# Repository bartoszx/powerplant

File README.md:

# POWERPANEL

_Opis funkcjonalny systemu — retro‑analogowy interfejs do Home Assistanta._

<p align="center">

</p>

_Kliknij, aby powiększyć. Wymiary panelu: 108 × 44 cm._ 

### Spis treści
- [1. Cel i koncepcja projektu](#1-cel-i-koncepcja-projektu)
- [2. Architektura i główne sekcje panelu](#2-architektura-i-główne-sekcje-panelu)
  - [2.1 Płyta główna (Main Board)](#21-płyta-główna-main-board)
  - [2.2 Moduły zewnętrzne](#22-moduły-zewnętrzne)
- [3. Mechanika i interfejs użytkownika](#3-mechanika-i-interfejs-użytkownika)
  - [3.1 Mierniki (sekcja)](#31-mierniki-sekcja)
- [4. Bloki funkcjonalne](#4-bloki-funkcjonalne)
  - [4.1 BLK_METER_ANALOG](#41-blk_meter_analog)
  - [4.2 BLK_METER_LED](#42-blk_meter_led)
  - [4.3 BLK_SWITCHES](#43-blk_switches)
  - [4.4 BLK_CONSOLE](#44-blk_console)
  - [4.5 BLK_SWITCH_LED](#45-blk_switch_led)
- [5. Komunikacja i zasilanie](#5-komunikacja-i-zasilanie)
- [6. Mechanika i ergonomia](#6-mechanika-i-ergonomia)
- [7. Uwagi konstrukcyjne](#7-uwagi-konstrukcyjne)
- [8. Podsumowanie](#8-podsumowanie)
- [9. Pliki schematów i PCB](#9-pliki-schematów-i-pcb)

---

## 1. Cel i koncepcja projektu
PowerPanel to fizyczna interpretacja możliwości systemu Home Assistant — 
czyli materialny, retro-analogowy interfejs do cyfrowego świata automatyki domowej.  

Nie jest to tylko panel energetyczny, ale wielosekcyjny moduł kontrolny i wizualizacyjny,
który odwzorowuje najważniejsze funkcje systemu HA w postaci fizycznych mierników, przycisków, 
przełączników, enkoderów i wskaźników świetlnych.

Celem jest uzyskanie wrażenia „żywego pulpitu sterowniczego” — 
panelu, który reaguje w czasie rzeczywistym na dane z Home Assistanta: energię, temperatury, stany stref, 
tryby pracy, alarmy, a także pozwala na bezpośrednią interakcję z systemem przez dotyk, pokrętła i przełączniki.

Całość utrzymana w stylistyce retro-industrialnej: 
mierniki URAL, bakelitowe przełączniki krzywkowe, suwakowe selektory, 
oraz matowy ekran LCD w stylu terminalowym, wpisujący się w analogowy klimat.

## 2. Architektura i główne sekcje panelu
System składa się z jednej płyty głównej (Main Board) i zestawu płytek peryferyjnych połączonych taśmami IDC.

### 2.1 Płyta główna (Main Board)
Zawiera wszystkie układy logiczne, analogowe i interfejsowe:
- ekspandery MCP23017 (wejścia, przyciski, enkodery),
- przetwornik DAC MCP4728 (sterowanie wskazówkami),
- bufory 74AHCT125 (3.3V → 5V dla WS2812),
- sterowniki ULN2803A (lampki i podświetlenia 12V),
- wzmacniacze LM358 (sterowniki prądowe wskaźników),
- złącza IDC dla modułów zewnętrznych.

<p align="center">
  
</p>

_Wizualizacja 3D płyty głównej (KiCad)._ 

Serce systemu stanowi Raspberry Pi 5, zamontowane bezpośrednio na płycie głównej (formą zbliżone do HAT), zapewniając komunikację, logikę i integrację z Home Assistantem.

Zasilanie:
- 12 V – sekcja mocy i lampek,
- 5 V – LED i DAC,
- 3.3 V – logika i magistrala I²C.
Masę podzielono na GND i GNDPWR (łączone w jednym punkcie).

### 2.2 Moduły zewnętrzne
- **NIXIE BOARD** – sterowanie lampami IN-14 (SPI, wysokonapięciowe).
- **METER PANEL** – z miernikami URAL i podświetleniem LED WS2812.
- **SWITCH PANEL** – sekcja przełączników trybów i zakresów czasowych.
- **CONSOLE PANEL** – centralny moduł z retro-ekranem LCD, enkoderami i kontrolkami.
- **ZONE ADM PANEL** – sekcja administracyjna stref (WAY / GARDEN / ALARM / OPEN).
- **INFO LED BOARD** – lampki 12 V (BIO, REC, OPEN, statusy).

Każdy moduł łączy się z płytą główną przez złącza IDC (10–34 pin).

## 3. Mechanika i interfejs użytkownika
Panel został podzielony na kilka stref funkcjonalnych, rozmieszczonych ergonomicznie na froncie obudowy:

- **Sekcja mierników (górna)** – pięć wskaźników URAL, 
  każdy z osobnym kanałem DAC i LED-podświetleniem.  
  Powyżej nich znajduje się przełącznik krzywkowy pozwalający zmieniać **skalę czasu** (LIVE / 1D / 7D / 14D / 1M / 6M / 12M).

- **Sekcja ZONE ADM (lewa dolna)** – przyciski i lampki strefowe, 
  np. WAY, GARDEN, ALARM, OPEN_PLACE.  
  Każda lampka 12 V jest sterowana z ULN2803A, a przycisk raportuje stan do HA przez I²C.

- **Centralna sekcja sterowania** – retro ekran LCD (terminalowy, tekstowy) 
  pokazujący status systemu i parametry; obok pokrętło **głośności (ENC_VOL)** z ring-LED, 
  przyciski **MODE_A/B/C** (zmiana trybu HA), oraz **przełącznik INPUT/OUTPUT**.

- **Sekcja energetyczna (prawa dolna)** – przełącznik krzywkowy głównego obiegu energetycznego (np. GRID / BAT / ISLAND),
  kontrolki statusu ładowania, oraz wskaźnik prądu zasilania głównego.

- **Selektor temperatury (prawy górny)** – przełącznik suwakowy wybierający, 
  które pomieszczenie ma być aktualnie wskazywane na mierniku temperatury (OUTDOOR / SALON / GAB / MIB / HEL / OLA).

Każdy element panelu ma fizyczne sprzężenie zwrotne: ruch wskazówki, światło LED, dźwięk enkodera, klik przełącznika.  
To czyni PowerPanel prawdziwie materialnym interfejsem Home Assistanta.

### 3.1 Mierniki (sekcja)
<p align="center">

</p>

_Tarcza, render sekcji i płytka z 30 micro‑LED — kliknij, aby powiększyć._

Na schemacie wyjścia prowadzące do poszczególnych mierników oznaczone są ich pierwotnymi parametrami (np. „2A”, „25mA”). Oznaczenia te służą pamięci i kalibracji podczas strojenia układu.

Każdy miernik, poza podstawowym działaniem pomiarowym, został zmodyfikowany:
- pod główną skalą umieszczono 30 programowalnych micro‑LEDów, pozwalających tworzyć efekty świetlne i subtelne wskazania kontekstowe,
- dodatkowy LED podświetla tarczę, poprawiając czytelność w słabym oświetleniu.

## 4. Bloki funkcjonalne

### 4.1 BLK_METER_ANALOG
Sterowanie pięcioma miernikami URAL.  
Układy: MCP4728 + LM358 + tranzystory 2N2222A.  
Każdy kanał DAC generuje napięcie (0–5 V) → LM358 → tranzystor NPN → cewka miernika.  
Filtry RC (100 nF + 10 kΩ) wygładzają wskazanie.  
Zasilanie 5 V, masa GNDPWR.  
Kanały: SENSE_A–E (MTR1–MTR5).

---

### 4.2 BLK_METER_LED
Sterowanie LED WS2812 i przyciskami 12 V w sekcji mierników i przycisków.  
Układy: MCP23017, ULN2803A ×2, 74AHCT125 ×2.  
Port A MCP23017 steruje ULN2803A (OUT_Mx_BL, URAL).  
Port B obsługuje przyciski i kontrolki (BTN_GATE, GARAGE, DOOR itd.).  
Bufory 74AHCT125 translatują sygnały LED 3.3V → 5V (MTR1–MTR5).  
Rezystory 68 Ω w szereg z liniami danych.  
Lampki 12 V sterowane z ULN2803A (open collector).  
GND i GNDPWR łączone w jednym punkcie.

---

### 4.3 BLK_SWITCHES
Sekcja 12 przełączników (tryby + zakresy) i 4 przyciski ZONE ADM.  
Układ: MCP23017 @ 0x21.  
Wejścia z pull-up 10 kΩ, C=100 nF do GND (debounce).  
Złącza:  
- IDC-20_SWITCH_BUS – tryby pracy (AUTO, BAT-SAVE, BLACKOUT, itp.)  
- IDC-12_SWITCH_ZONE_BUS – strefy (WAY, GARDEN, ALARM, OPEN)  
Stany czytane przez I²C.

---

### 4.4 BLK_CONSOLE
Centralny panel z trzema enkoderami i przyciskami MODE.  
Układ: MCP23017 @ 0x23.  
Pull-up 10 kΩ + C=100 nF (debounce).  
Linia INT_CONSOLED (opcjonalne przerwanie).  
Złącze IDC-16_CONSOLE:  
- MODE_A/B/C – wybór trybów  
- ENC_VOL, ENC_TOP, ENC_BOTTOM – enkodery  
- VOL_RING_DATA – dane LED pierścienia  
- przyciski push – w osi enkoderów

---

### 4.5 BLK_SWITCH_LED
Buforowanie danych LED (74AHCT125) i sterowanie lampkami 12 V (ULN2803A).  
Złącza:  
- IDC-10_SWITCH_LED_DATA – LED WS2812  
- IDC-6_ZONE_INFO_12V – lampki BIO / REC / OPEN  
Sygnały 3.3V z RPi → bufory 5V → taśmy WS2812.  
Rezystory R58–R60 = 100 Ω.  
Wspólna masa GND↔GNDPWR.

---

## 5. Komunikacja i zasilanie
Magistrala I²C:
- MCP23017 (SWITCHES) – 0x21  
- MCP23017 (CONSOLE) – 0x23  
- MCP23017 (METER_LED) – 0x20  
- MCP4728 (METER_ANALOG) – 0x60  

Zasilanie:
- +12 V – lampki i przekaźniki  
- +5 V – LED WS2812, DAC  
- +3.3 V – logika i I²C  
- GND / GNDPWR – wspólny punkt (separacja prądów)

---

## 6. Mechanika i ergonomia
- Wskaźniki URAL – analogowe sprzężenie ruchu z DAC.  
- LED – efekt tła i animacje w rytmie danych HA.  
- Przyciski 12 V – kontrola stref / trybów.  
- Enkodery – głośność, tryby, ustawienia.  
- Krzywkowe i suwakowe selektory – wybór skali czasu, temperatury, źródła energii.  
- Retro LCD – dane systemowe i statusy HA.  

- Panel frontowy z blachy stalowej zostanie poddany kontrolowanemu procesowi postarzenia (patyna, przetarcia, delikatnie pordzewiałe krawędzie), aby uzyskać wygląd starego, przemysłowego urządzenia.

Każdy element ma bezpośrednią funkcję w HA i wizualne potwierdzenie akcji.

---

## 7. Uwagi konstrukcyjne
- Separacja GND / GNDPWR.  
- Stitching vias między planami mas.  
- 100 nF przy każdym układzie.  
- Rezystory szeregowe 68–100 Ω przy WS2812.  
- C = 1000 µF przy zasilaniu LED.  
- LM358 i MCP4728 zasilane z 5 V (z odniesieniem do GNDPWR).  
- Bufory 74AHCT125 – VCC = 5 V, Vih ≥ 2 V.

---

## 8. Podsumowanie
PowerPanel to fizyczny interfejs Home Assistanta — 
łączący dane z automatyki, energii, stref, mediów i systemów bezpieczeństwa w jednym, dotykalnym pulpicie.

Zawiera:
- 5 analogowych mierników URAL (DAC-sterowane),
- 3 enkodery + ring LED,
- 20+ LED WS2812,
- 20 przycisków i przełączników,
- kontrolki 12 V,
- wyświetlacz LCD retro,
- oraz krzywkowe i suwakowe selektory trybów.

Stanowi pomost między cyfrowym systemem automatyki a fizycznym światem.

---

## 9. Pliki schematów i PCB

**Źródło prawdy (source of truth)** dla hardware'u: **`hardware/pcb/powerplant.kicad_sch`**.  
Ten plik może się aktualizować; dokumentacja, konfiguracja i kod powinny być z nim zsynchronizowane.

Pliki KiCad znajdują się w katalogu `hardware/pcb`:

- Główne pliki projektu: `hardware/pcb/powerplant.kicad_sch`, `hardware/pcb/powerplant.kicad_pcb`
- Schematy bloków: 
  - `hardware/pcb/BLK_BUTTONS.kicad_sch`
  - `hardware/pcb/BLK_CONSOLE.kicad_sch`
  - `hardware/pcb/BLK_METER_LED.kicad_sch`
  - `hardware/pcb/BLK_SWITCH_LED.kicad_sch`
  - `hardware/pcb/BLK_SWITCHES.kicad_sch`

Pełne drzewo plików sprzętowych: `hardware/pcb/`.

**Moduł sterowania miernikami** (osobny projekt KiCad, pliki w Dropbox: `kicad/powerplant/modul-miernikow.*`):

- Opis schematu (weryfikacja MCP): [`doc/modul-miernikow-opis-schematu.md`](doc/modul-miernikow-opis-schematu.md)
- Wklejka na schemat KiCad: [`doc/modul-miernikow-wklejka-schemat.txt`](doc/modul-miernikow-wklejka-schemat.txt)

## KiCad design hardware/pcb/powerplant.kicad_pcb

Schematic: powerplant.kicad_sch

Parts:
A1: RaspberryPi_Pico; RaspberryPi_Pico_Common_Unspecified
C1, C8, C11, C13, C18, C20: 4.7 µF; R_1206_3216Metric
C2, C3, C6, C7, C10, C12, C16, C17, C19, C59, C60, C61: 100 nF; C_0603_1608Metric
C4, C29: 10 µF; R_1206_3216Metric
C5, C9, C14, C15, C21, C22: 680 pF; C_0603_1608Metric
C53, C58: 1 µF; C_0603_1608Metric
C54: 4.7 µF; C_0603_1608Metric
FB2: FerriteBead 600 Ω @ 100 MHz; L_1206_3216Metric_Pad1.22x1.90mm_HandSolder
J2: J_AUX; JST_PH_B8B-PH-K_1x08_P2.00mm_Vertical
J3: VL53L0X; JST_PH_B4B-PH-K_1x04_P2.00mm_Vertical
J4: J_LCD_PWR; JST_PH_B2B-PH-K_1x02_P2.00mm_Vertical
J5: SPARE; JST_PH_B8B-PH-K_1x08_P2.00mm_Vertical
J6: RPi_GPIO; RPI_Hat_B_NOPCB
J16: 14_NIXIE_BUS; IDC-Header_2x07_P2.54mm_Vertical
J19: J_LIGHT; JST_PH_B4B-PH-K_1x04_P2.00mm_Vertical
J21: IDC-10_METER_SIG; IDC-Header_2x05_P2.54mm_Vertical
J22: J_IN; SolderWire-1sqmm_1x02_P5.4mm_D1.4mm_OD2.7mm
J23: J_OUT; SolderWire-1sqmm_1x02_P5.4mm_D1.4mm_OD2.7mm
J24: POWER IN 12V; BarrelJack_Horizontal
NT1: NetTie_2; NetTie-2_THT_Pad1.0mm
Q1, Q2, Q3, Q4, Q5, Q6: IRLZ44N; TO-220-3_Vertical
R1, R5, R9, R10, R21, R22: 10 kΩ; R_0603_1608Metric
R2, R6, R11, R12, R23, R24: 100 Ω; R_1206_3216Metric_Pad1.30x1.75mm_HandSolder
R3, R15: Rlimit 100 kΩ; R_0603_1608Metric
R4, R8, R13, R14, R25, R26: Rpd 100 kΩ; R_0603_1608Metric
R7: Rlimit 150 kΩ; R_0603_1608Metric
R16, R29, R30: Rlimit 10 Ω; R_0603_1608Metric
R17, R20: RSENSE 200 kΩ; R_0603_1608Metric
R18: RSENSE 140 kΩ; R_0603_1608Metric
R19: RSENSE 500 Ω; R_0603_1608Metric
R27, R28: RSENSE 820 Ω; R_0603_1608Metric
R62, R63: 4.7kΩ; R_0603_1608Metric
U1, U4: MCP4728; MSOP-10_3x3mm_P0.5mm
U2, U3, U10: LM358_DFN; DFN-8-1EP_2x2mm_P0.5mm_EP1.05x1.75mm
U14: TPS22917DBV; SOT-23-6

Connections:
+3.3V: FB2.1, J5.1, J6.1 (3.3V), R62.1, R63.1; also elsewhere on the board
+5V: A1.40 (VBUS), C6.2, C16.2, C53.2, J3.4, J6.2 (5V), J16.1, J16.10, J23.1, U1.1 (VDD), U4.1 (VDD), U14.1 (VIN); also elsewhere on the board
+12V: C3.1, C4.1, C29.1, C60.1, C61.1, J22.1, J24.1, R3.1, R7.1, R15.1, R16.1, R29.2, R30.2, U2.8 (V+), U3.8 (V+), U10.8 (V+); also elsewhere on the board
/AUX_I2S_LRCLK: J2.2, J6.35 (BCM19_MISO_PCM_FS)
/AUX_I2S_RX: J2.4, J6.38 (BCM20_MOSI_PCM_DI)
/AUX_I2S_TX: J2.3, J6.40 (BCM21_SCLK_PCM_DO)
/AUX_SCL: J2.6, J3.2, J6.5 (BCM3_SCL), J19.4, R62.2, U1.2 (SCL), U4.2 (SCL); also elsewhere on the board
/AUX_SDA: J2.5, J3.3, J6.3 (BCM2_SDA), J19.3, R63.2, U1.3 (SDA), U4.3 (SDA); also elsewhere on the board
/BLK_CONSOLE/INT_CONSOLE: J6.21 (BCM9_MISO); also elsewhere on the board
/BLK_METER_LED/CTRL_GARAGE_LED: J6.16 (BCM23); also elsewhere on the board
/BLK_METER_LED/CTRL_GATE_LED: J6.18 (BCM24); also elsewhere on the board
/BLK_METER_LED/GPIO_LED1: A1.9 (GPIO6); also elsewhere on the board
/BLK_METER_LED/GPIO_LED2: A1.10 (GPIO7); also elsewhere on the board
/BLK_METER_LED/GPIO_LED3: A1.11 (GPIO8); also elsewhere on the board
/BLK_METER_LED/GPIO_LED4: A1.12 (GPIO9); also elsewhere on the board
/BLK_METER_LED/GPIO_LED5: A1.14 (GPIO10); also elsewhere on the board
/BLK_METER_LED/GPIO_VOL_RING: A1.7 (GPIO5); also elsewhere on the board
/BLK_SWITCH_LED/LED_MODE_DATA_IN: A1.5 (GPIO3); also elsewhere on the board
/BLK_SWITCH_LED/LED_RANGE_DATA_IN: A1.4 (GPIO2); also elsewhere on the board
/BLK_SWITCH_LED/LED_TEMP_DATA_IN: A1.6 (GPIO4); also elsewhere on the board
/CTRL_INFO_BIO: J6.15 (BCM22); also elsewhere on the board
/CTRL_INFO_OPEN: J6.11 (BCM17); also elsewhere on the board
/CTRL_INFO_REC: J6.13 (BCM27); also elsewhere on the board
/GP0_TX_PICO: A1.1 (GPIO0), J6.10 (BCM15_RXD)
/GP1_RX_PICO: A1.2 (GPIO1), J6.8 (BCM14_TXD)
/GP11: A1.15 (GPIO11), J5.3
/GP12: A1.16 (GPIO12), J5.4
/GP13: A1.17 (GPIO13), J5.5
/GP14: A1.19 (GPIO14), J5.6
/GP15: A1.20 (GPIO15), J5.7
/GP16: A1.21 (GPIO16), J5.8
/J_METER_1A+: J21.5, R15.2
/J_METER_5mA+: J21.3, R7.2
/J_METER_25uA+: J21.1, R3.2
/J_METER_PLUS_MINUS+: J21.9, Q5.2 (D), R29.1
/J_METER_TBC+: J21.7, R16.2
/LCD_PWR_EN: J6.12 (BCM18_PCM_C), U14.3 (ON)
/METER-: J21.2, Q1.2 (D)
/MR: J21.10, Q6.2 (D), R30.1
/NIXIE_CS1: J6.24 (BCM8_CE0), J16.5
/NIXIE_CS2: J6.26 (BCM7_CE1), J16.6
/NIXIE_CS3: J6.22 (BCM25), J16.7
/NIXIE_CS4: J6.27 (BCM0_ID_SD), J16.8
/SENSE_A: C5.2, Q1.3 (S), R17.2, U2.2 (-)
/SENSE_B: C9.2, Q2.3 (S), R18.2, U2.6 (-)
/SENSE_C: C14.2, Q3.3 (S), R19.2, U3.2 (-)
/SENSE_D: C15.2, Q4.3 (S), R20.2, U3.6 (-)
/SENSE_E1: C21.2, Q5.3 (S), R27.1, U10.2 (-)
/SENSE_E2: C22.2, Q6.3 (S), R28.1, U10.6 (-)
/SPI_MOSI: J6.19 (BCM10_MOSI), J16.3
/SPI_SCLK: J6.23 (BCM11_SCLK), J16.4
/VIN_FILT_A: R1.1, U1.6 (VOUTA), U2.3 (+)
/VIN_FILT_B: R5.1, U1.7 (VOUTB), U2.5 (+)
/VIN_FILT_C: R9.1, U1.8 (VOUTC), U3.3 (+)
/VIN_FILT_D: R10.1, U1.9 (VOUTD), U3.5 (+)
/VIN_FILT_E1: R21.1, U4.6 (VOUTA), U10.3 (+)
/VIN_FILT_E2: R22.1, U4.7 (VOUTB), U10.5 (+)
GND: A1.3 (GND), A1.8 (GND), A1.13 (GND), A1.18 (GND), A1.23 (GND), A1.28 (GND), A1.38 (GND), C6.1, C16.1, C53.1, C54.2, C58.1, C59.1, J2.7, J3.1, J4.2, J5.2, J6.39 (GND), J16.2, J16.11, J16.12, J19.2, J23.2, NT1.1, U1.10 (VSS), U4.10 (VSS), U14.2 (GND); also elsewhere on the board
GNDPWR: C1.2, C2.1, C3.2, C4.2, C7.1, C8.2, C10.1, C11.2, C12.1, C13.2, C17.1, C18.2, C19.1, C20.2, C29.2, C60.2, C61.2, J22.2, J24.2, NT1.2, R4.2, R8.2, R13.2, R14.2, R17.1, R18.1, R19.1, R20.1, R25.1, R26.1, R27.2, R28.2, U2.4 (V-), U2.9 (PAD), U3.4 (V-), U3.9 (PAD), U10.4 (V-), U10.9 (PAD); also elsewhere on the board
unnamed: C1.1, C2.2, R1.2
unnamed: C5.1, R2.1, U2.1
unnamed: C7.2, C8.1, R5.2
unnamed: C9.1, R6.1, U2.7
unnamed: C10.2, C11.1, R9.2
unnamed: C12.2, C13.1, R10.2
unnamed: C14.1, R11.1, U3.1
unnamed: C15.1, R12.1, U3.7
unnamed: C17.2, C18.1, R21.2
unnamed: C19.2, C20.1, R22.2
unnamed: C21.1, R23.1, U10.1
unnamed: C22.1, R24.1, U10.7
unnamed: C54.1, J4.1, U14.6 (VOUT)
unnamed: C58.2, C59.2, FB2.2, J19.1
unnamed: J21.4, Q2.2 (D)
unnamed: J21.6, Q3.2 (D)
unnamed: J21.8, Q4.2 (D)
unnamed: Q1.1 (G), R2.2, R4.1
unnamed: Q2.1 (G), R6.2, R8.1
unnamed: Q3.1 (G), R11.2, R13.1
unnamed: Q4.1 (G), R12.2, R14.1
unnamed: Q5.1 (G), R23.2, R25.2
unnamed: Q6.1 (G), R24.2, R26.2

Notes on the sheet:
⚙️ BLK_METER_ANALOG - opis funkcjonalny ======================================== Sekcja: Tory sterowania i pomiaru wskaźników analogowych (5 kanałów VU / mA / wskazówki URAL) Układy główne: U3A-U3E, U10A-U10C - LM358 (wzmacniacze operacyjne) U1 - MCP4728 (4-kanałowy DAC I²C, 12-bit) Q1-Q5 - tranzys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
CZUJNIK SWIATLA
NIXIE zew board https://github.com/dekuNukem/exixe po SPI

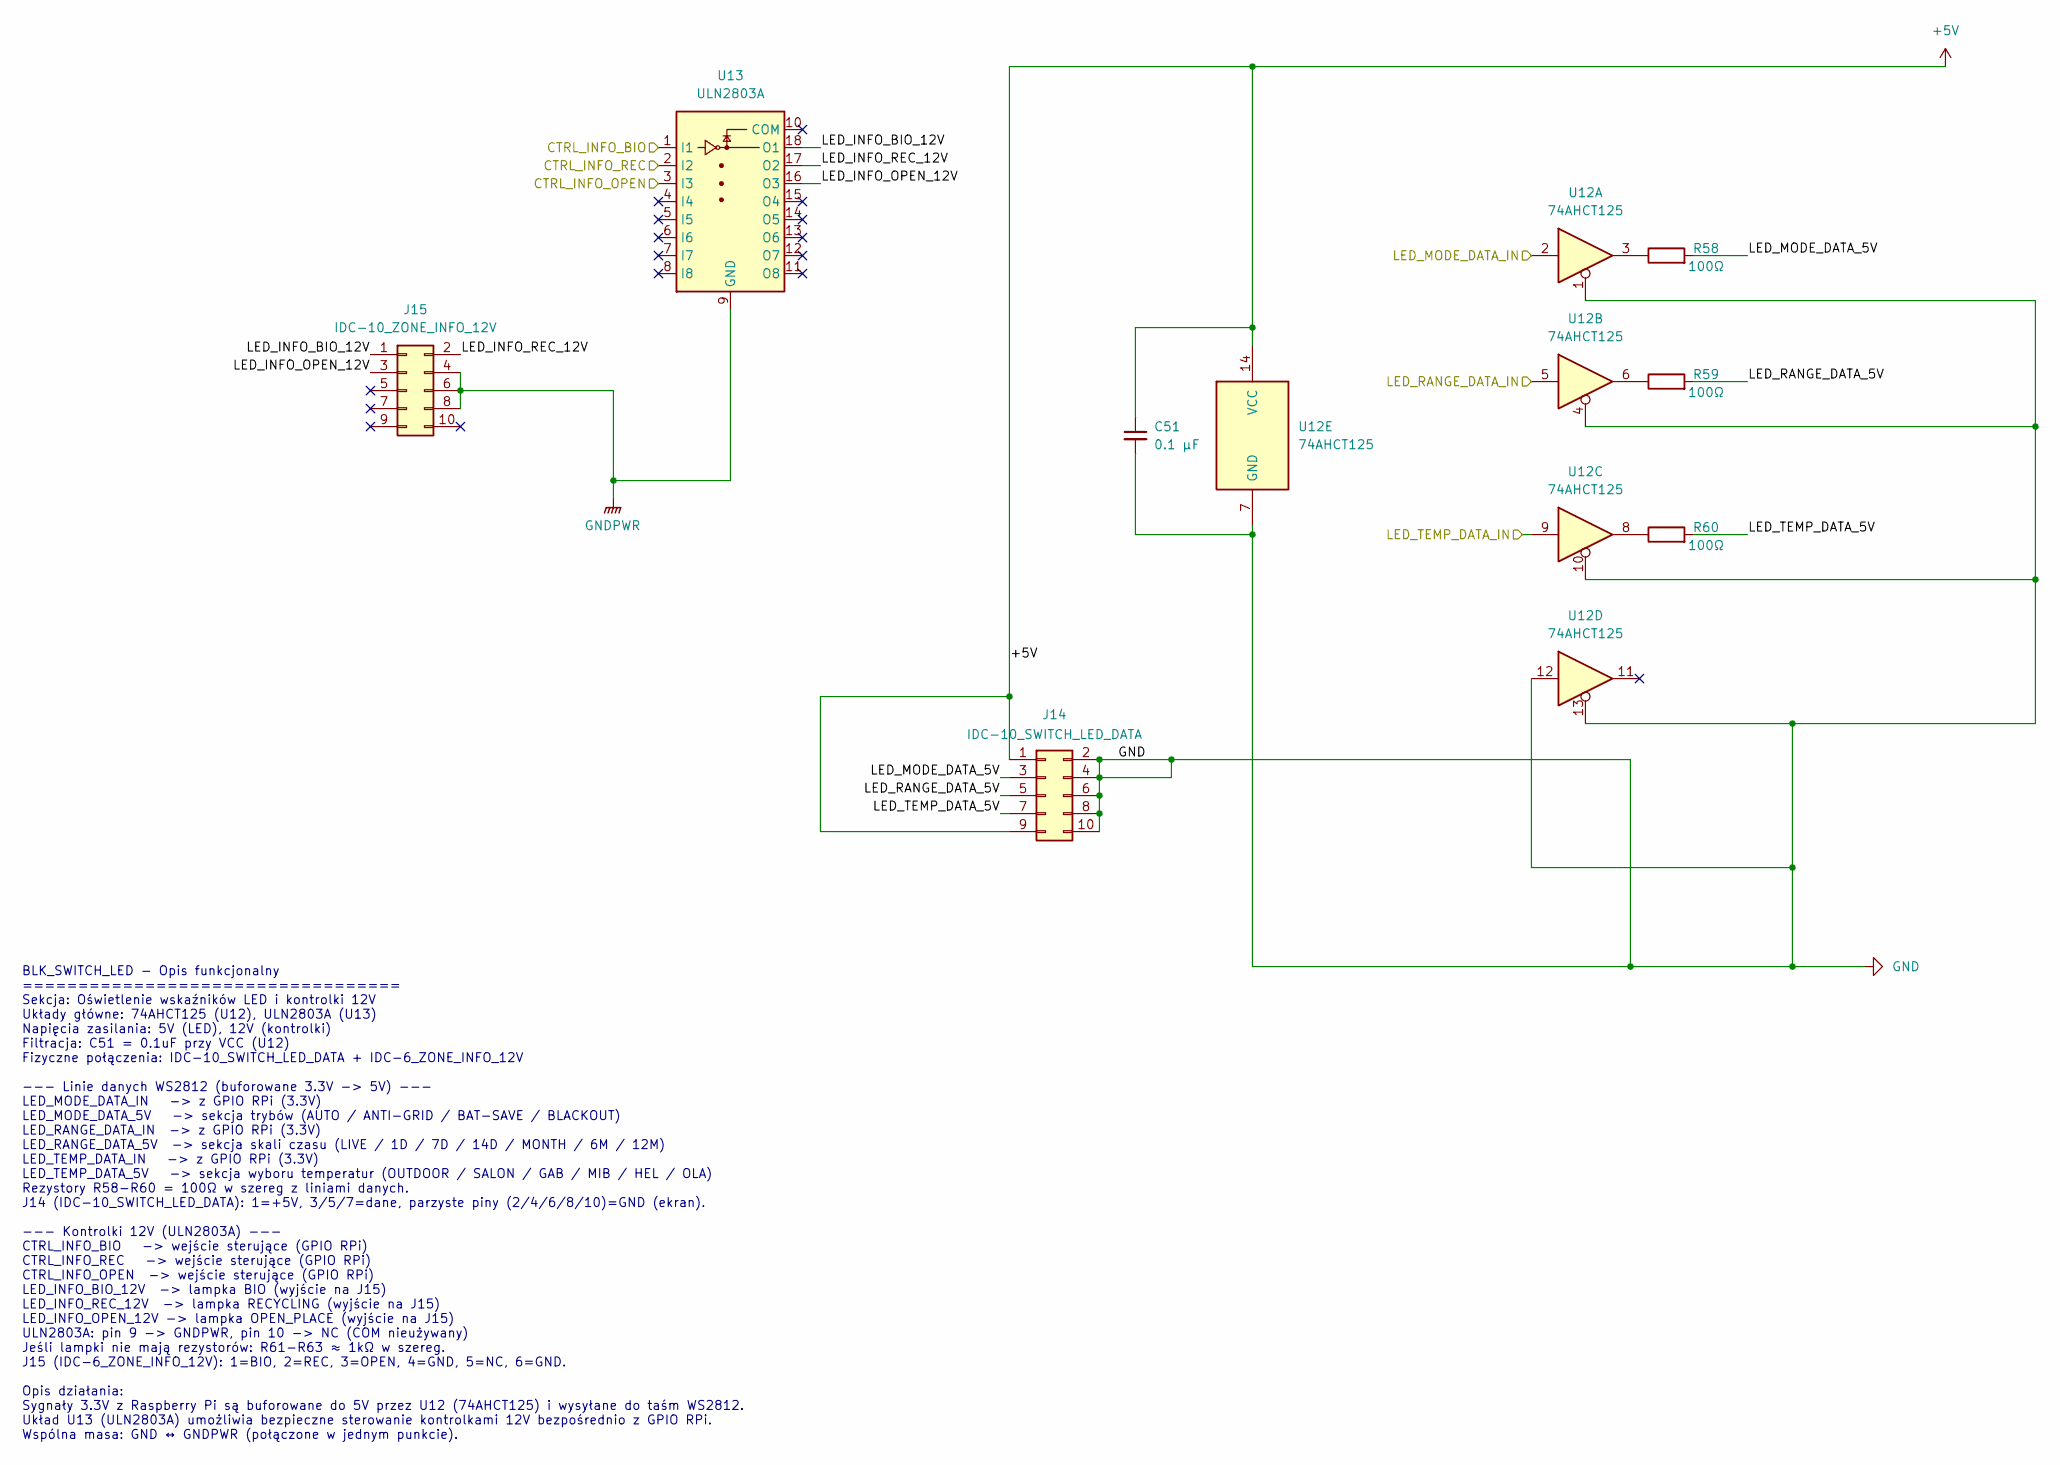
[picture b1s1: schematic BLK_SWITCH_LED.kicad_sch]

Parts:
C51: 0.1 µF; C_0603_1608Metric
J14: IDC-10_SWITCH_LED_DATA; IDC-Header_2x05_P2.54mm_Vertical
J15: IDC-10_ZONE_INFO_12V; IDC-Header_2x05_P2.54mm_Vertical
R58, R59, R60: 100Ω; R_0603_1608Metric
U12: 74AHCT125; SOIC-14_3.9x8.7mm_P1.27mm
U13: ULN2803A; SSOP-18_4.4x6.5mm_P0.65mm

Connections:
+5V: C51.1, J14.1, J14.9, U12.14 (VCC); also elsewhere on the board
/BLK_SWITCH_LED/LED_INFO_BIO_12V: J15.1, U13.18 (O1)
/BLK_SWITCH_LED/LED_INFO_OPEN_12V: J15.3, U13.16 (O3)
/BLK_SWITCH_LED/LED_INFO_REC_12V: J15.2, U13.17 (O2)
/BLK_SWITCH_LED/LED_MODE_DATA_5V: J14.3, R58.2
/BLK_SWITCH_LED/LED_MODE_DATA_IN: U12.2; also elsewhere on the board
/BLK_SWITCH_LED/LED_RANGE_DATA_5V: J14.5, R59.2
/BLK_SWITCH_LED/LED_RANGE_DATA_IN: U12.5; also elsewhere on the board
/BLK_SWITCH_LED/LED_TEMP_DATA_5V: J14.7, R60.2
/BLK_SWITCH_LED/LED_TEMP_DATA_IN: U12.9; also elsewhere on the board
/CTRL_INFO_BIO: U13.1 (I1); also elsewhere on the board
/CTRL_INFO_OPEN: U13.3 (I3); also elsewhere on the board
/CTRL_INFO_REC: U13.2 (I2); also elsewhere on the board
GND: C51.2, J14.2, J14.4, J14.6, J14.8, J14.10, U12.1, U12.4, U12.7 (GND), U12.10, U12.12, U12.13; also elsewhere on the board
GNDPWR: J15.4, J15.6, J15.8, U13.9 (GND); also elsewhere on the board
unnamed: R58.1, U12.3
unnamed: R59.1, U12.6
unnamed: R60.1, U12.8

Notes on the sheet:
BLK_SWITCH_LED - Opis funkcjonalny ================================== Sekcja: Oświetlenie wskaźników LED i kontrolki 12V Układy główne: 74AHCT125 (U12), ULN2803A (U13) Napięcia zasilania: 5V (LED), 12V (kontrolki) Filtracja: C51 = 0.1uF przy VCC (U12) Fizyczne połączenia: IDC-10_SWITCH_LED_DATA + I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

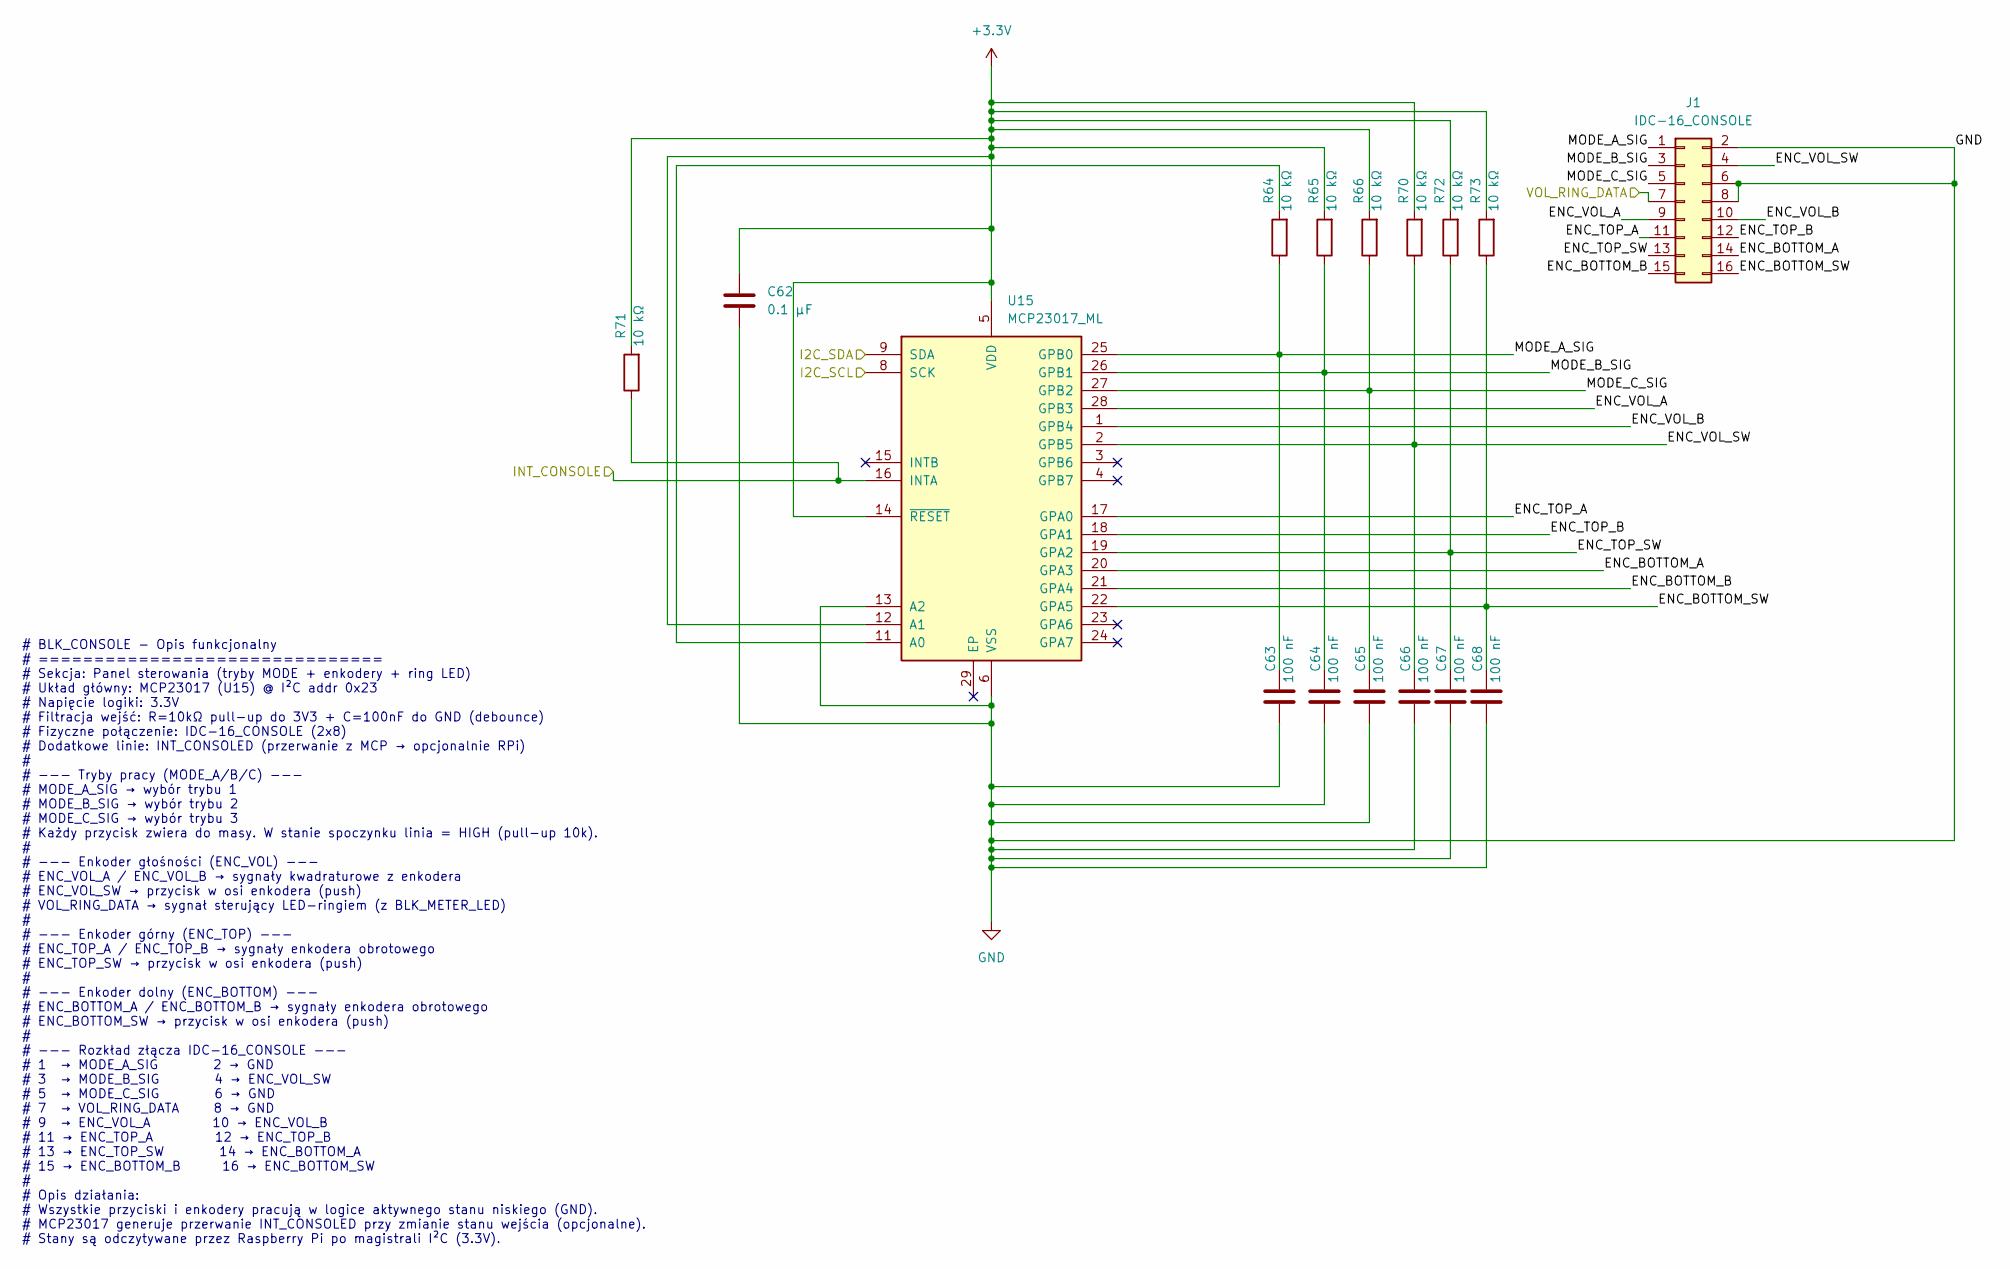
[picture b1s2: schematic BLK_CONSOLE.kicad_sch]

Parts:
C62: 0.1 µF; C_1206_3216Metric_Pad1.33x1.80mm_HandSolder
C63, C64, C65, C66, C67, C68: 100 nF; C_1206_3216Metric_Pad1.33x1.80mm_HandSolder
J1: IDC-16_CONSOLE; IDC-Header_2x08_P2.54mm_Vertical
R64, R65, R66, R70, R71, R72, R73: 10 kΩ; R_1206_3216Metric_Pad1.30x1.75mm_HandSolder
U15: MCP23017_ML; QFN-28-1EP_6x6mm_P0.65mm_EP4.25x4.25mm

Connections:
+3.3V: C62.2, R65.2, R66.2, R70.2, R71.2, R72.2, R73.2, U15.5 (VDD), U15.12 (A1), U15.14 (~RESET); also elsewhere on the board
/AUX_SCL: U15.8 (SCK); also elsewhere on the board
/AUX_SDA: U15.9 (SDA); also elsewhere on the board
/BLK_CONSOLE/ENC_BOTTOM_A: J1.14, U15.20 (GPA3)
/BLK_CONSOLE/ENC_BOTTOM_B: J1.15, U15.21 (GPA4)
/BLK_CONSOLE/ENC_BOTTOM_SW: C68.2, J1.16, R73.1, U15.22 (GPA5)
/BLK_CONSOLE/ENC_TOP_A: J1.11, U15.17 (GPA0)
/BLK_CONSOLE/ENC_TOP_B: J1.12, U15.18 (GPA1)
/BLK_CONSOLE/ENC_TOP_SW: C67.2, J1.13, R72.1, U15.19 (GPA2)
/BLK_CONSOLE/ENC_VOL_A: J1.9, U15.28 (GPB3)
/BLK_CONSOLE/ENC_VOL_B: J1.10, U15.1 (GPB4)
/BLK_CONSOLE/ENC_VOL_SW: C66.2, J1.4, R70.1, U15.2 (GPB5)
/BLK_CONSOLE/INT_CONSOLE: R71.1, U15.16 (INTA); also elsewhere on the board
/BLK_CONSOLE/MODE_A_SIG: C63.2, J1.1, R64.1, U15.25 (GPB0)
/BLK_CONSOLE/MODE_B_SIG: C64.2, J1.3, R65.1, U15.26 (GPB1)
/BLK_CONSOLE/MODE_C_SIG: C65.2, J1.5, R66.1, U15.27 (GPB2)
/BLK_CONSOLE/VOL_RING_DATA: J1.7; also elsewhere on the board
GND: C62.1, C63.1, C64.1, C65.1, C66.1, C67.1, C68.1, J1.2, J1.6, J1.8, U15.6 (VSS), U15.13 (A2); also elsewhere on the board
unnamed: R64.2, U15.11 (A0)

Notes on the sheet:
# BLK_CONSOLE - Opis funkcjonalny # =============================== # Sekcja: Panel sterowania (tryby MODE + enkodery + ring LED) # Układ główny: MCP23017 (U15) @ I²C addr 0x23 # Napięcie logiki: 3.3V # Filtracja wejść: R=10kΩ pull-up do 3V3 + C=100nF do GND (debounce) # Fizyczne połączenie: IDC-16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

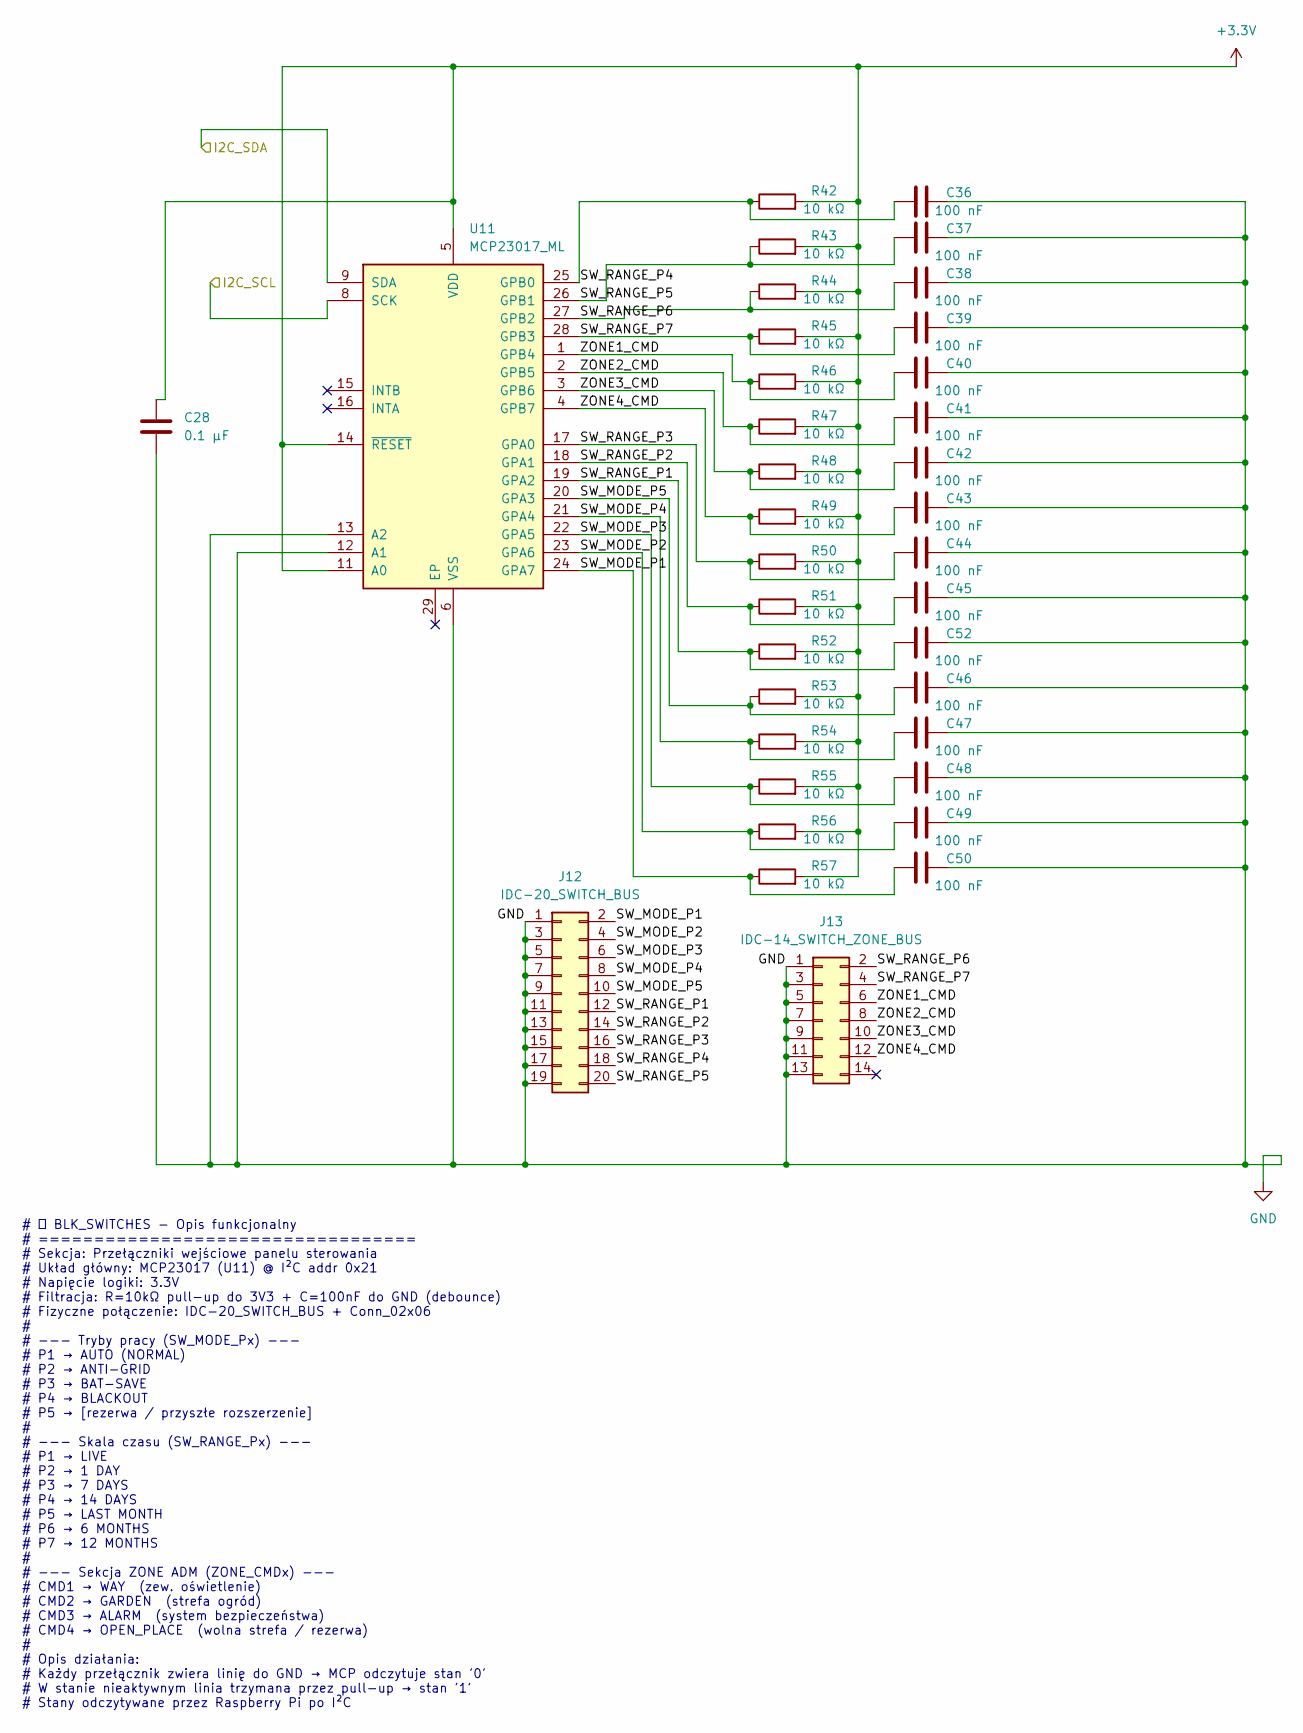
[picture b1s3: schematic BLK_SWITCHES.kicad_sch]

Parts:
C28: 0.1 µF; C_1206_3216Metric_Pad1.33x1.80mm_HandSolder
C36, C37, C38, C39, C40, C41, C42, C43, C44, C45, C46, C47, C48, C49, C50, C52: 100 nF; C_1206_3216Metric_Pad1.33x1.80mm_HandSolder
J12: IDC-20_SWITCH_BUS; IDC-Header_2x10_P2.54mm_Vertical
J13: IDC-14_SWITCH_ZONE_BUS; IDC-Header_2x07_P2.54mm_Vertical
R42, R43, R44, R45, R46, R47, R48, R49, R50, R51, R52, R53, R54, R55, R56, R57: 10 kΩ; R_1206_3216Metric_Pad1.30x1.75mm_HandSolder
U11: MCP23017_ML; QFN-28-1EP_6x6mm_P0.65mm_EP4.25x4.25mm

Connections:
+3.3V: C28.2, R42.2, R43.2, R44.2, R45.2, R46.2, R47.2, R48.2, R49.2, R50.2, R51.2, R52.2, R53.2, R54.2, R55.2, R56.2, R57.2, U11.5 (VDD), U11.11 (A0), U11.14 (~RESET); also elsewhere on the board
/AUX_SCL: U11.8 (SCK); also elsewhere on the board
/AUX_SDA: U11.9 (SDA); also elsewhere on the board
/BLK_SWITCHES/SW_MODE_P1: C50.1, J12.2, R57.1, U11.24 (GPA7)
/BLK_SWITCHES/SW_MODE_P2: C49.1, J12.4, R56.1, U11.23 (GPA6)
/BLK_SWITCHES/SW_MODE_P3: C48.1, J12.6, R55.1, U11.22 (GPA5)
/BLK_SWITCHES/SW_MODE_P4: C47.1, J12.8, R54.1, U11.21 (GPA4)
/BLK_SWITCHES/SW_MODE_P5: C46.1, J12.10, R53.1, U11.20 (GPA3)
/BLK_SWITCHES/SW_RANGE_P1: C52.1, J12.12, R52.1, U11.19 (GPA2)
/BLK_SWITCHES/SW_RANGE_P2: C45.1, J12.14, R51.1, U11.18 (GPA1)
/BLK_SWITCHES/SW_RANGE_P3: C44.1, J12.16, R50.1, U11.17 (GPA0)
/BLK_SWITCHES/SW_RANGE_P4: C36.1, J12.18, R42.1, U11.25 (GPB0)
/BLK_SWITCHES/SW_RANGE_P5: C37.1, J12.20, R43.1, U11.26 (GPB1)
/BLK_SWITCHES/SW_RANGE_P6: C38.1, J13.2, R44.1, U11.27 (GPB2)
/BLK_SWITCHES/SW_RANGE_P7: C39.1, J13.4, R45.1, U11.28 (GPB3)
/BLK_SWITCHES/ZONE1_CMD: C40.1, J13.6, R46.1, U11.1 (GPB4)
/BLK_SWITCHES/ZONE2_CMD: C41.1, J13.8, R47.1, U11.2 (GPB5)
/BLK_SWITCHES/ZONE3_CMD: C42.1, J13.10, R48.1, U11.3 (GPB6)
/BLK_SWITCHES/ZONE4_CMD: C43.1, J13.12, R49.1, U11.4 (GPB7)
GND: C28.1, C36.2, C37.2, C38.2, C39.2, C40.2, C41.2, C42.2, C43.2, C44.2, C45.2, C46.2, C47.2, C48.2, C49.2, C50.2, C52.2, J12.1, J12.3, J12.5, J12.7, J12.9, J12.11, J12.13, J12.15, J12.17, J12.19, J13.1, J13.3, J13.5, J13.7, J13.9, J13.11, J13.13, U11.6 (VSS), U11.12 (A1), U11.13 (A2); also elsewhere on the board

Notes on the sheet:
# 🟡 BLK_SWITCHES - Opis funkcjonalny # ================================== # Sekcja: Przełączniki wejściowe panelu sterowania # Układ główny: MCP23017 (U11) @ I²C addr 0x21 # Napięcie logiki: 3.3V # Filtracja: R=10kΩ pull-up do 3V3 + C=100nF do GND (debounce) # Fizyczne połączenie: IDC-20_SWITCH_BUS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

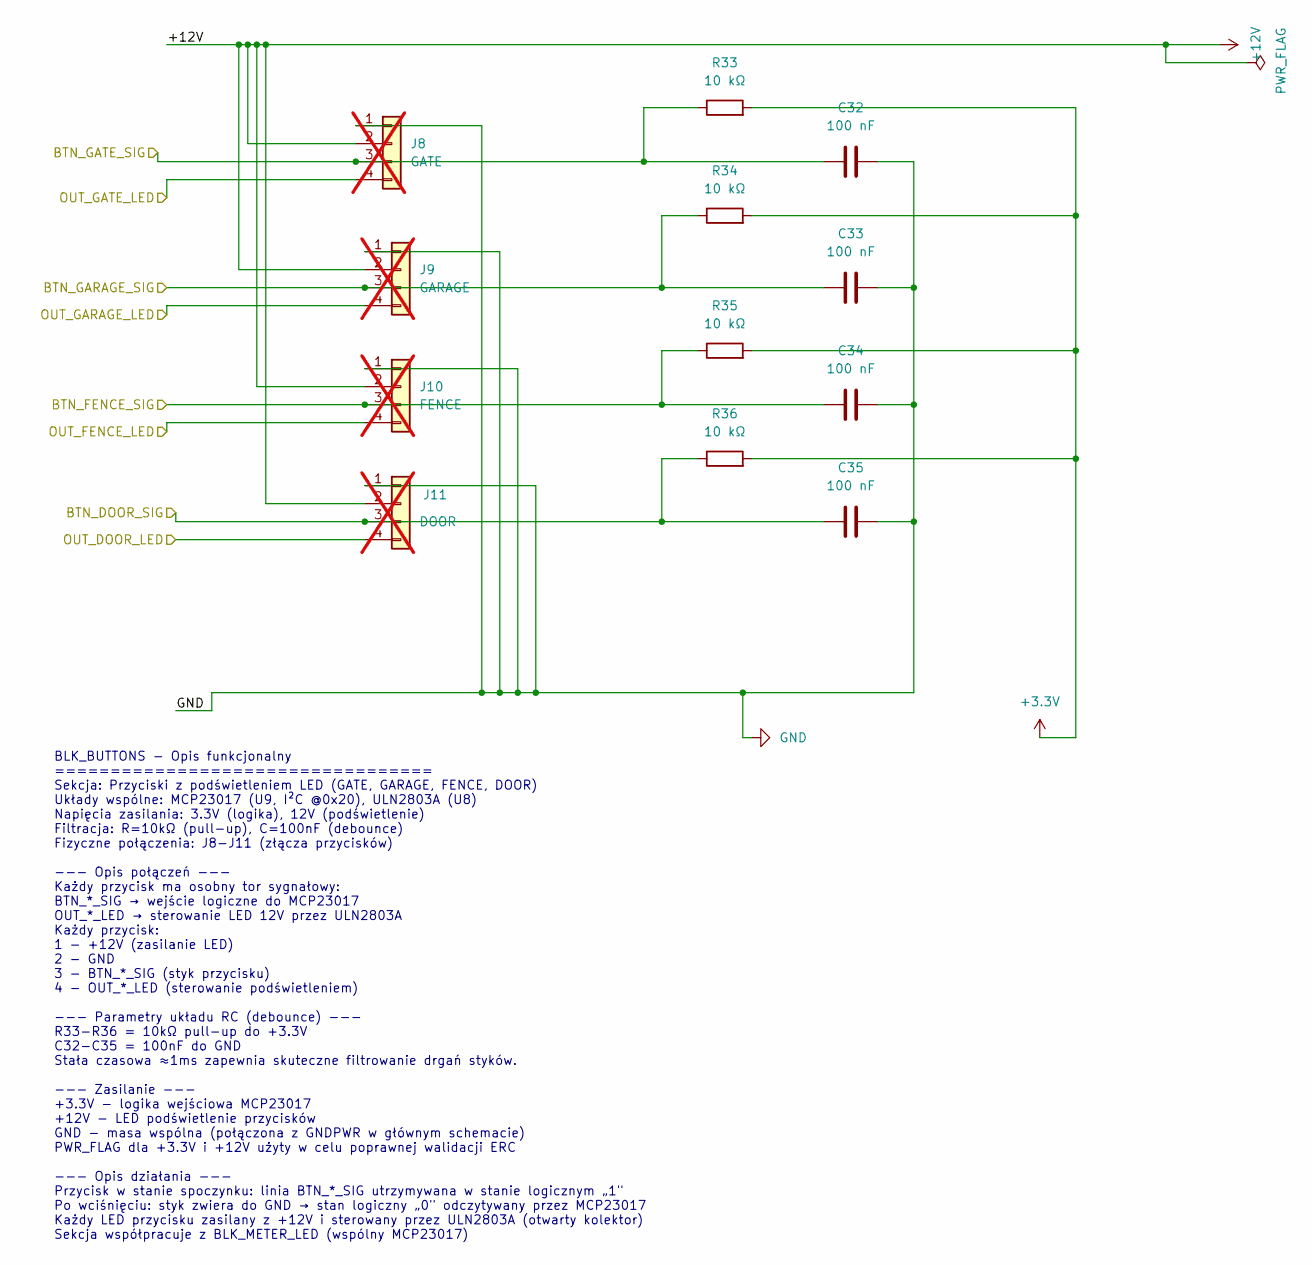
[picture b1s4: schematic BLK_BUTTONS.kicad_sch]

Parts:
C32, C33, C34, C35: 100 nF; C_1206_3216Metric_Pad1.33x1.80mm_HandSolder
J8: GATE; not fitted
J9: GARAGE; not fitted
J10: FENCE; not fitted
J11: DOOR; not fitted
R33, R34, R35, R36: 10 kΩ; R_1206_3216Metric_Pad1.30x1.75mm_HandSolder

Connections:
+3.3V: R33.2, R34.2, R35.2, R36.2; also elsewhere on the board
/BLK_BUTTONS/BTN_DOOR_SIG: C35.1, J11.3, R36.1; also elsewhere on the board
/BLK_BUTTONS/BTN_FENCE_SIG: C34.2, J10.3, R35.1; also elsewhere on the board
/BLK_BUTTONS/BTN_GARAGE_SIG: C33.2, J9.3, R34.1; also elsewhere on the board
/BLK_BUTTONS/BTN_GATE_SIG: C32.2, J8.3, R33.1; also elsewhere on the board
GND: C32.1, C33.1, C34.1, C35.2, J8.1, J9.1, J10.1, J11.1; also elsewhere on the board
unnamed: J8.2, J9.2, J10.2, J11.2

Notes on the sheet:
BLK_BUTTONS - Opis funkcjonalny ================================== Sekcja: Przyciski z podświetleniem LED (GATE, GARAGE, FENCE, DOOR) Układy wspólne: MCP23017 (U9, I²C @0x20), ULN2803A (U8) Napięcia zasilania: 3.3V (logika), 12V (podświetlenie) Filtracja: R=10kΩ (pull-up), C=100nF (debounce) Fizycz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
